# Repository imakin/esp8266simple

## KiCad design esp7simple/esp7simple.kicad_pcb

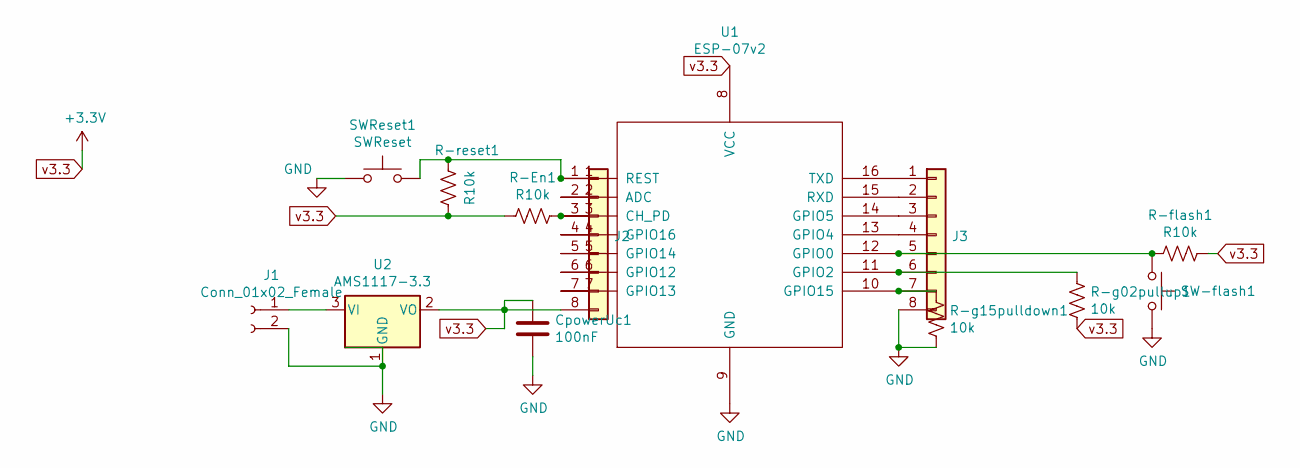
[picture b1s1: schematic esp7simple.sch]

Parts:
CpowerUc1: 100nF; C_1206_3216Metric
J1: Conn_01x02_Female; PinHeader_1x02_P2.54mm_Vertical
J2, J3: PinHeader_1x08_P2.54mm_Vertical
R-En1: R10k; R_0805_2012Metric
R-flash1: R10k; R_0805_2012Metric
R-g02pullup1, R-g15pulldown1: 10k; R_0805_2012Metric
R-reset1: R10k; R_0805_2012Metric
SW-flash1: SWflash; SW_PUSH_6mm
SWReset1: SWReset; SW_PUSH_6mm
U1: ESP-07v2
U2: AMS1117-3.3; SOT-223-3_TabPin2

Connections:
GND: CpowerUc1.2, J1.2, J3.8, R-g15pulldown1.2, SW-flash1.2, SWReset1.1, U1.9 (GND), U2.1 (GND)
unnamed: J1.1, U2.3 (VI)
unnamed: J2.1, R-reset1.2, SWReset1.2, U1.1 (REST)
unnamed: J2.2, U1.2 (ADC)
unnamed: J2.3, R-En1.1, U1.3 (CH_PD)
unnamed: J2.4, U1.4 (GPIO16)
unnamed: J2.5, U1.5 (GPIO14)
unnamed: J2.6, U1.6 (GPIO12)
unnamed: J2.7, U1.7 (GPIO13)
unnamed: J3.1, U1.16 (TXD)
unnamed: J3.2, U1.15 (RXD)
unnamed: J3.3, U1.14 (GPIO5)
unnamed: J3.4, U1.13 (GPIO4)
unnamed: J3.5, R-flash1.2, SW-flash1.1, U1.12 (GPIO0)
unnamed: J3.6, R-g02pullup1.1, U1.11 (GPIO2)
unnamed: J3.7, R-g15pulldown1.1, U1.10 (GPIO15)
v3.3: CpowerUc1.1, J2.8, R-En1.2, R-flash1.1, R-g02pullup1.2, R-reset1.1, U1.8 (VCC), U2.2 (VO)

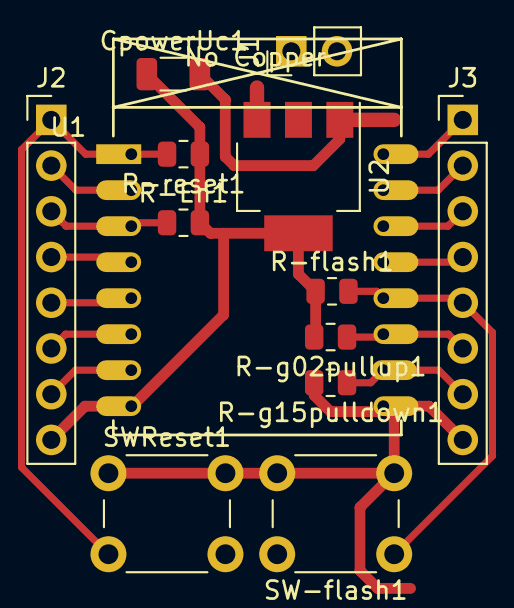
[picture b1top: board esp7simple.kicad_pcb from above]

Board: 2 copper layers, 13 parts (0 on the bottom side), 17 nets.

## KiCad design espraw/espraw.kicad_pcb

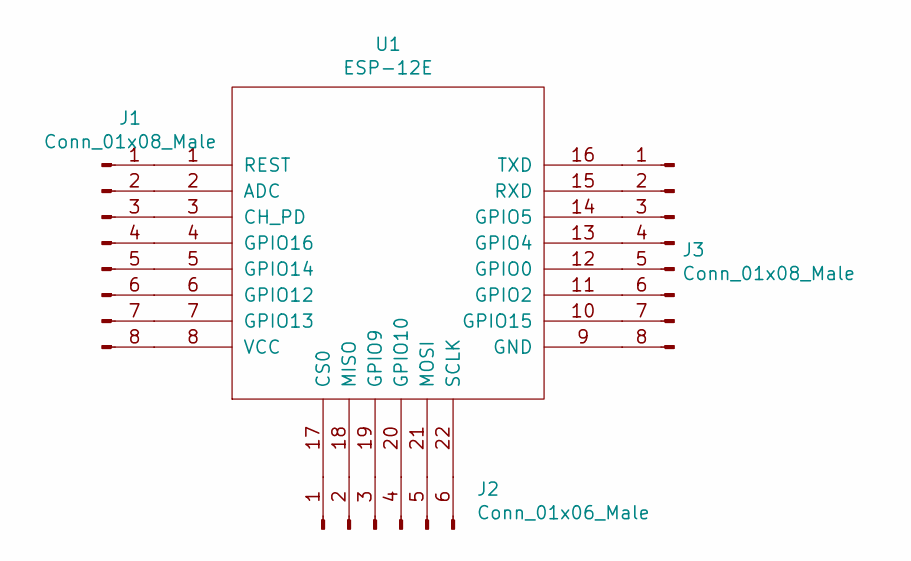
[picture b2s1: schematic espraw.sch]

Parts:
J1, J3: Conn_01x08_Male; PinHeader_1x08_P2.54mm_Vertical
J2: Conn_01x06_Male; PinHeader_1x06_P2.54mm_Vertical
U1: ESP-12E

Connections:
unnamed: J1.1, U1.1 (REST)
unnamed: J1.2, U1.2 (ADC)
unnamed: J1.3, U1.3 (CH_PD)
unnamed: J1.4, U1.4 (GPIO16)
unnamed: J1.5, U1.5 (GPIO14)
unnamed: J1.6, U1.6 (GPIO12)
unnamed: J1.7, U1.7 (GPIO13)
unnamed: J1.8, U1.8 (VCC)
unnamed: J2.1, U1.17 (CS0)
unnamed: J2.2, U1.18 (MISO)
unnamed: J2.3, U1.19 (GPIO9)
unnamed: J2.4, U1.20 (GPIO10)
unnamed: J2.5, U1.21 (MOSI)
unnamed: J2.6, U1.22 (SCLK)
unnamed: J3.1, U1.16 (TXD)
unnamed: J3.2, U1.15 (RXD)
unnamed: J3.3, U1.14 (GPIO5)
unnamed: J3.4, U1.13 (GPIO4)
unnamed: J3.5, U1.12 (GPIO0)
unnamed: J3.6, U1.11 (GPIO2)
unnamed: J3.7, U1.10 (GPIO15)
unnamed: J3.8, U1.9 (GND)

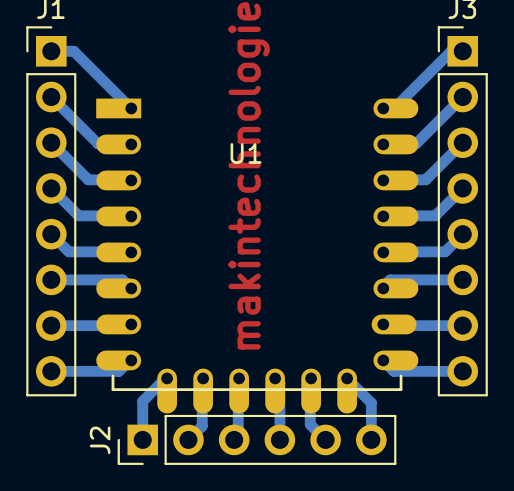
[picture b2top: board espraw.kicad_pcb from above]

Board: 2 copper layers, 4 parts (0 on the bottom side), 22 nets.

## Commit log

2020-12-14 add kicad files
2020-12-15 add module
2020-12-15 add gitignore
2020-12-15 finish board for esp12
2020-12-16 add esp7simple board
2020-12-17 add esp7 simple variant
